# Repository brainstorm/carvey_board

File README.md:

Carvey smartclamp<sup>tm</sup> homebrew PCB enhancement with autoleveling support
=====

<a href="https://PCBs.io/share/zOVlY"></img></a>

This is a working KiCad response to the [inventables thread on how to height probe a PCB](https://discuss.inventables.com/t/height-probing-a-pcb-on-carvey/21139/10) with [the Carvey](https://www.inventables.com/technologies/Carvey) and [Grbl Chillipeppr with autolevel plugin](http://chilipeppr.com/jpadie). Also a way to rapidly and inexpensively iterate on my PCB prototyping projects without long shipping times.

The new board has a convenient exposed zone outside the metallic clamp so that common alligator clips can be attached without long overhang wires as seen above in the pictures.

Two CNC-ready files created with my own OSX/Python3/Qt5-compatible version of [FlatCAM](https://bitbucket.org/brainstorm/flatcam/src/master/) are available under [homefab](https://github.com/brainstorm/carvey_board/tree/master/homefab/cnc), along with the accompanying KiCad gerbers. You will need a 0.1mm drill for PCB isolation routing and a 3.13mm drill for the board cutout (tipically included in the Carvey drill kit).

If there's enough interest in getting those boards made by a fab I can setup a tindie run perhaps? File an issue if so to gauge interest, otherwise, this is open hardware, download the Gerbers and have fun! ;)

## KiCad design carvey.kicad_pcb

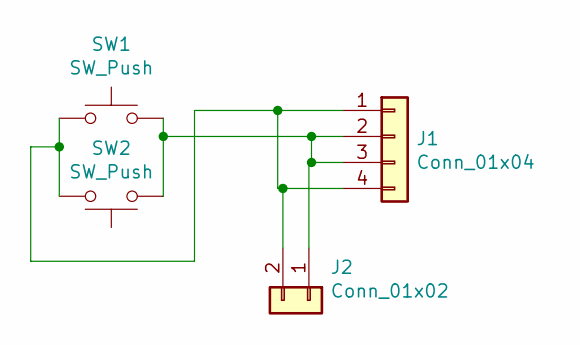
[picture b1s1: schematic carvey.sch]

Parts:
J1: Conn_01x04; JST_PH_S4B-PH-SM4-TB_04x2.00mm_Angled
J2: Conn_01x02; TouchSlider-2_10x7mm
SW1, SW2: SW_Push; SW_SPST_B3U-1000P

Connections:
unnamed: J1.1, J1.4, J2.2, SW1.1, SW2.2
unnamed: J1.2, J1.3, J2.1, SW1.2, SW2.1

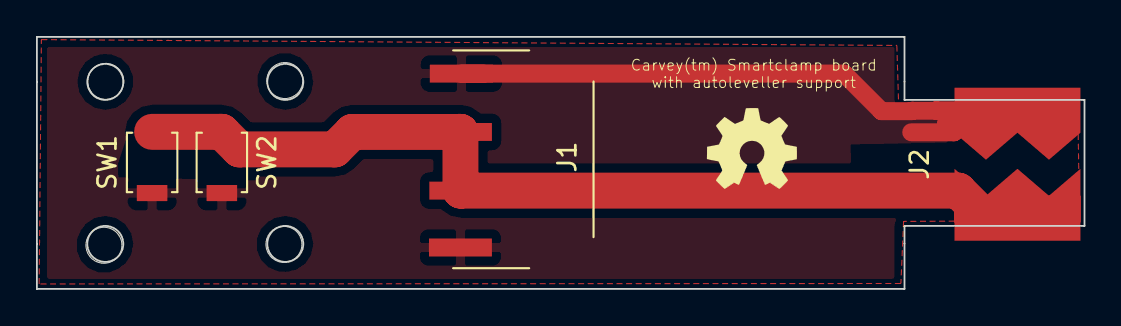
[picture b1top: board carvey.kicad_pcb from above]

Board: 2 copper layers, 58.2 x 14.0 mm, 5 parts (0 on the bottom side), 2 nets.

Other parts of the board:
LOGO_OSHW_silkscreen_5mm: val**; LOGO_OSHW_silkscreen_5mm

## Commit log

2018-04-23 Initial commit, supports cables for autolevelling
2018-04-25 Added holes, carved it with Carvey itself, without autoleveling
2018-04-25 Plain board to be cut out from the copper clad
2018-04-25 Carvey cutout board G-Code
2018-04-26 Add board outline only to be cut by CNC
2018-04-26 Track too near pad
2018-05-17 Add new board outline with external overhang for alligator clips, need to add the pads
2018-05-17 New version of the board with protruding pads for the alligator clips
2018-05-17 Add README/explanation of this
2018-05-17 Decent markdown/html... hopefully working imgur gif?
2018-05-17 Please imgur/github, show my nice gif?
2018-05-17 Wrong imgur link?
2018-05-17 Is the internet full of lies?: https://stackoverflow.com/questions/37750270/unable-to-embed-a-gif-on-imgur-to-a-readme-md-on-github
2018-05-17 i prefix on imgur url?
2018-05-17 Align to center
2018-05-17 Imgur gone after markdown align center?
2018-05-17 Enough with Markdown, switch to pure html
2018-05-19 Typo as seen in https://hackaday.com/tag/autoleveling/
2018-05-19 State the option to have people use it as-is, without the need to spend a cent... after all it is just a board with two buttons
2018-05-31 Add and mention ready-to-CNC .nc files to make this project on the Carvey itself
2018-10-28 Make sure naming is compatible with pcbs.io... they still do not fully support KiCad apparently
2018-10-28 Add pcbs.io link
2018-10-28 More visible banner at the beginning of the README
